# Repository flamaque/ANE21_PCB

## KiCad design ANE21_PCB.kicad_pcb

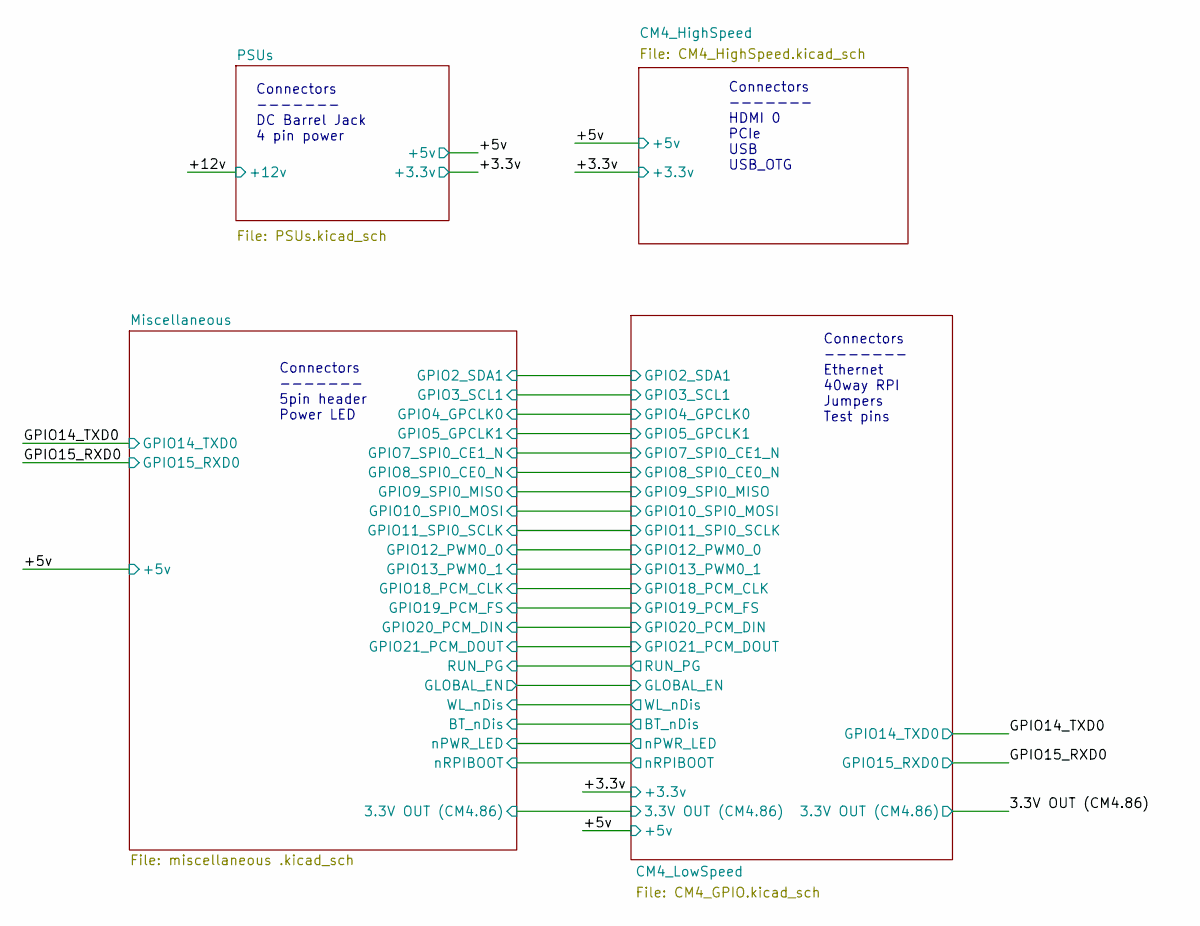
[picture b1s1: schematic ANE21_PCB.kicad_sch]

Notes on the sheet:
Connectors ------- DC Barrel Jack 4 pin power
Connectors ------- Ethernet 40way RPI Jumpers Test pins
Connectors ------- 5pin header Power LED
Connectors ------- HDMI 0 PCIe USB USB_OTG

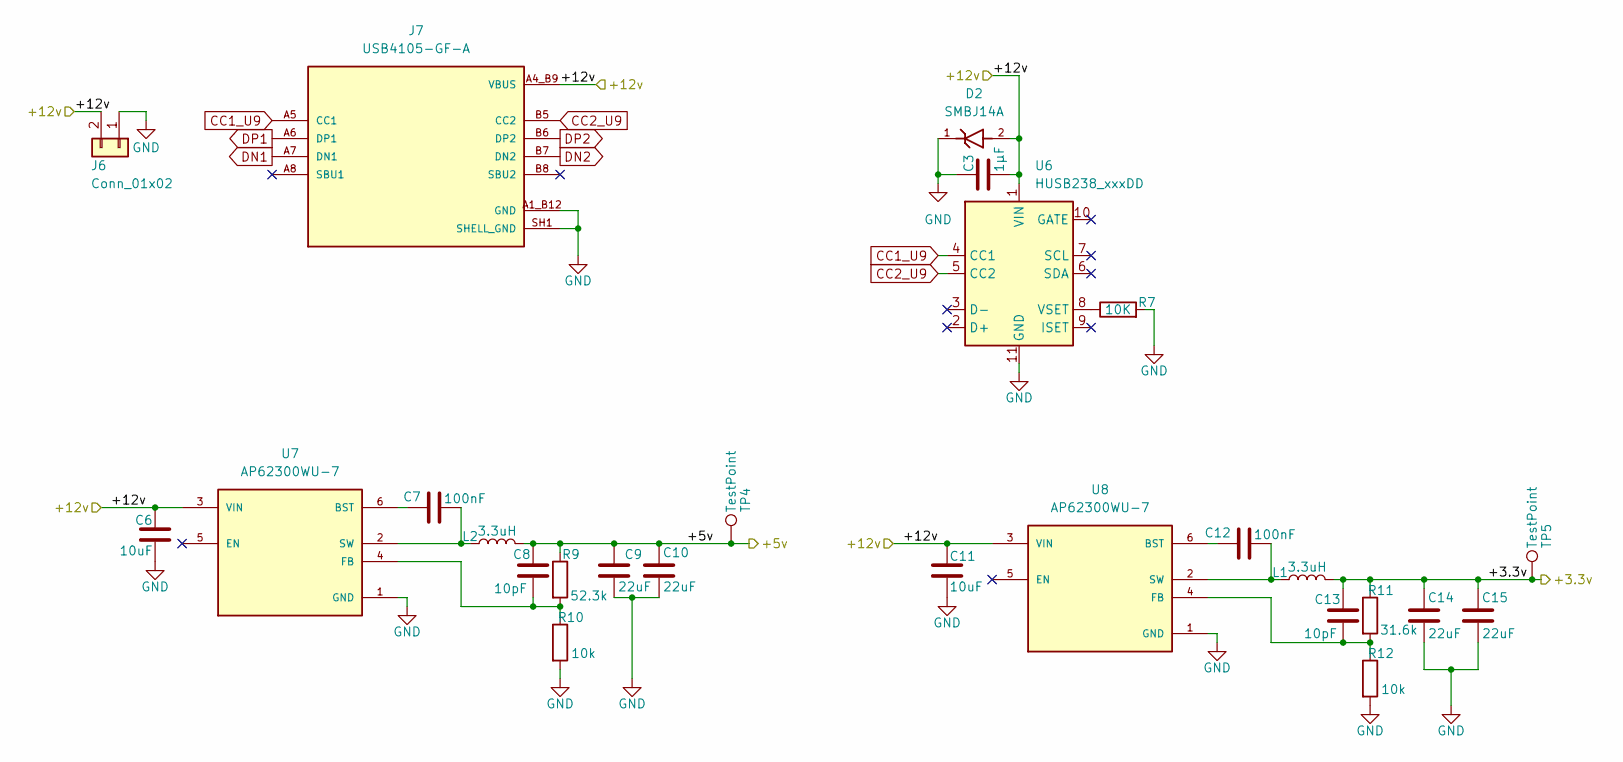
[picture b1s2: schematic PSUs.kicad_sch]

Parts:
C3: 1µF; C_0402_1005Metric_Pad0.74x0.62mm_HandSolder
C6, C11: 10uF; C_0402_1005Metric_Pad0.74x0.62mm_HandSolder
C7, C12: 100nF; C_0402_1005Metric_Pad0.74x0.62mm_HandSolder
C8, C13: 10pF; C_0402_1005Metric_Pad0.74x0.62mm_HandSolder
C9, C10, C14, C15: 22uF; C_0402_1005Metric_Pad0.74x0.62mm_HandSolder
D2: SMBJ14A; DIOM5436X261N; PARTREV JC.07/04/25 v4
J6: Conn_01x02; TerminalBlock_PhoenixTerminalBlock_Phoenix_MKDS-1,5-2-5.08_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
J7: USB4105-GF-A; GCT_USB4105-GF-A; PARTREV B4
L1, L2: 3.3uH; IND_1255AY-3R3N=P3
R7: 10K; R_0402_1005Metric_Pad0.72x0.64mm_HandSolder
R9: 52.3k; R_0402_1005Metric_Pad0.72x0.64mm_HandSolder
R10, R12: 10k; R_0402_1005Metric_Pad0.72x0.64mm_HandSolder
R11: 31.6k; R_0402_1005Metric_Pad0.72x0.64mm_HandSolder
TP4, TP5: TestPoint; TestPoint_Pad_2.0x2.0mm
U6: HUSB238_xxxDD; WDFN-10-1EP_3x3mm_P0.5mm_EP1.8x2.5mm
U7, U8: AP62300WU-7; SOT95P280X100-6N; PARTREV Rev. 3 - 2; DigiKey_Part_Number 31-AP62300WU-7CT-ND

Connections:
/+3.3v: C13.2, C14.2, C15.2, L1.2, R11.1, TP5.1; also elsewhere on the board
CC1_U9: J7.A5 (CC1), U6.4 (CC1); also elsewhere on the board
CC2_U9: J7.B5 (CC2), U6.5 (CC2); also elsewhere on the board
GND: C3.1, C6.2, C9.1, C10.1, C11.2, C14.1, C15.1, D2.1, J6.1, J7.A1_B12 (GND), J7.B1_A12 (GND), J7.SH1 (SHELL_GND), J7.SH2 (SHELL_GND), J7.SH3 (SHELL_GND), J7.SH4 (SHELL_GND), R7.2, R10.2, R12.2, U6.11 (GND), U7.1 (GND), U8.1 (GND); also elsewhere on the board
unnamed: R7.1, U6.8 (VSET)
unnamed: C7.1, U7.6 (BST)
unnamed: C8.1, R9.2, R10.1, U7.4 (FB)
unnamed: C7.2, L2.1, U7.2 (SW)
unnamed: C12.1, U8.6 (BST)
unnamed: C13.1, R11.2, R12.1, U8.4 (FB)
unnamed: C12.2, L1.1, U8.2 (SW)
VBUS: C8.2, C9.2, C10.2, L2.2, R9.1, TP4.1; also elsewhere on the board
VBUS-PD: C3.2, C6.1, C11.1, D2.2, J6.2, J7.A4_B9 (VBUS), J7.B4_A9 (VBUS), U6.1 (VIN), U7.3 (VIN), U8.3 (VIN); also elsewhere on the board

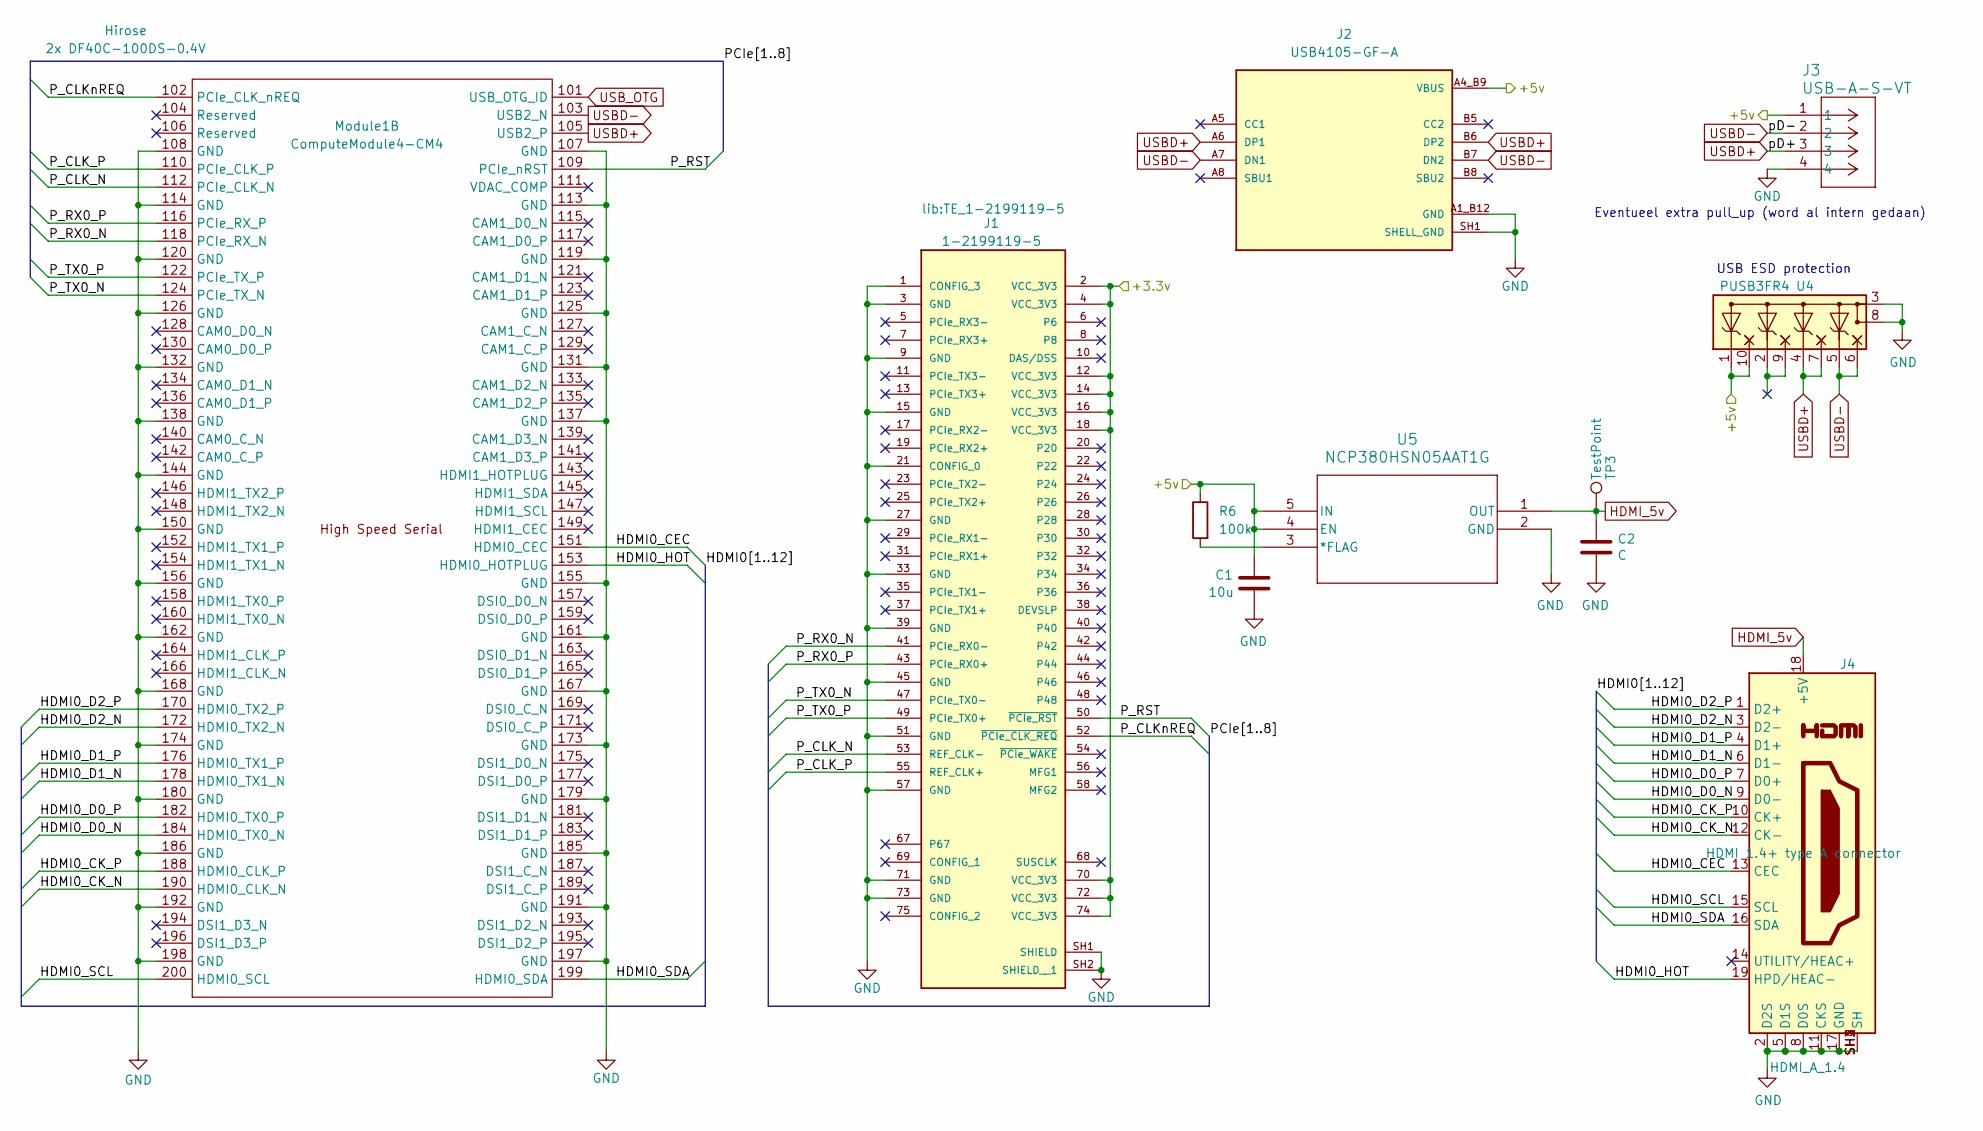
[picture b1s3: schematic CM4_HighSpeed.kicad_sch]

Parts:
C1: 10u; C_0402_1005Metric_Pad0.74x0.62mm_HandSolder; Part Description 0.1uF 10% 16V Ceramic Capacitor X7R 040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
C2: C; C_0402_1005Metric_Pad0.74x0.62mm_HandSolder; Part Description 0.1uF 10% 16V Ceramic Capacitor X7R 040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
J1: 1-2199119-5; TE_1-2199119-5
J2: USB4105-GF-A; GCT_USB4105-GF-A; PARTREV B4
J3: USB-A-S-VT; CONN_USB-A-S-VT_ADM
J4: HDMI_A_1.4; AMPHENOL_10029449-111RLF; Part Description HDMI Connector, Right Angle, 19 Contact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
Module1: ComputeModule4-CM4; Raspberry-Pi-4-Compute-Module
R6: 100k; R_0402_1005Metric_Pad0.72x0.64mm_HandSolder
TP3: TestPoint; TestPoint_Pad_2.0x2.0mm
U4: PUSB3FR4; SOT1176-1
U5: NCP380HSN05AAT1G; TSOP-5_ONS

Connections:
/+3.3v: J1.2 (VCC_3V3), J1.4 (VCC_3V3), J1.12 (VCC_3V3), J1.14 (VCC_3V3), J1.16 (VCC_3V3), J1.18 (VCC_3V3), J1.70 (VCC_3V3), J1.72 (VCC_3V3), J1.74 (VCC_3V3); also elsewhere on the board
/CM4_HighSpeed/HDMI0_CEC: J4.13 (CEC), Module1.151 (HDMI0_CEC)
/CM4_HighSpeed/HDMI0_CK_N: J4.12 (CK-), Module1.190 (HDMI0_CLK_N)
/CM4_HighSpeed/HDMI0_CK_P: J4.10 (CK+), Module1.188 (HDMI0_CLK_P)
/CM4_HighSpeed/HDMI0_D0_N: J4.9 (D0-), Module1.184 (HDMI0_TX0_N)
/CM4_HighSpeed/HDMI0_D0_P: J4.7 (D0+), Module1.182 (HDMI0_TX0_P)
/CM4_HighSpeed/HDMI0_D1_N: J4.6 (D1-), Module1.178 (HDMI0_TX1_N)
/CM4_HighSpeed/HDMI0_D1_P: J4.4 (D1+), Module1.176 (HDMI0_TX1_P)
/CM4_HighSpeed/HDMI0_D2_N: J4.3 (D2-), Module1.172 (HDMI0_TX2_N)
/CM4_HighSpeed/HDMI0_D2_P: J4.1 (D2+), Module1.170 (HDMI0_TX2_P)
/CM4_HighSpeed/HDMI0_HOT: J4.19 (HPD/HEAC-), Module1.153 (HDMI0_HOTPLUG)
/CM4_HighSpeed/HDMI0_SCL: J4.15 (SCL), Module1.200 (HDMI0_SCL)
/CM4_HighSpeed/HDMI0_SDA: J4.16 (SDA), Module1.199 (HDMI0_SDA)
/CM4_HighSpeed/P_CLK_N: J1.53 (REF_CLK-), Module1.112 (PCIe_CLK_N)
/CM4_HighSpeed/P_CLK_P: J1.55 (REF_CLK+), Module1.110 (PCIe_CLK_P)
/CM4_HighSpeed/P_CLKnREQ: J1.52 (~PCIe_CLK_REQ), Module1.102 (PCIe_CLK_nREQ)
/CM4_HighSpeed/P_RST: J1.50 (~PCIe_RST), Module1.109 (PCIe_nRST)
/CM4_HighSpeed/P_RX0_N: J1.41 (PCIe_RX0-), Module1.118 (PCIe_RX_N)
/CM4_HighSpeed/P_RX0_P: J1.43 (PCIe_RX0+), Module1.116 (PCIe_RX_P)
/CM4_HighSpeed/P_TX0_N: J1.47 (PCIe_TX0-), Module1.124 (PCIe_TX_N)
/CM4_HighSpeed/P_TX0_P: J1.49 (PCIe_TX0+), Module1.122 (PCIe_TX_P)
GND: C1.2, C2.2, J1.1 (CONFIG_3), J1.3 (GND), J1.9 (GND), J1.15 (GND), J1.21 (CONFIG_0), J1.27 (GND), J1.33 (GND), J1.39 (GND), J1.45 (GND), J1.51 (GND), J1.57 (GND), J1.71 (GND), J1.73 (GND), J1.SH1 (SHIELD), J1.SH2 (SHIELD__1), J2.A1_B12 (GND), J2.B1_A12 (GND), J2.SH1 (SHELL_GND), J2.SH2 (SHELL_GND), J2.SH3 (SHELL_GND), J2.SH4 (SHELL_GND), J3.4, J4.2 (D2S), J4.5 (D1S), J4.8 (D0S), J4.11 (CKS), J4.17 (GND), J4.SH1 (SH), J4.SH2 (SH), J4.SH3 (SH), J4.SH4 (SH), Module1.107 (GND), Module1.108 (GND), Module1.113 (GND), Module1.114 (GND), Module1.119 (GND), Module1.120 (GND), Module1.125 (GND), Module1.126 (GND), Module1.131 (GND), Module1.132 (GND), Module1.137 (GND), Module1.138 (GND), Module1.144 (GND), Module1.150 (GND), Module1.155 (GND), Module1.156 (GND), Module1.161 (GND), Module1.162 (GND), Module1.167 (GND), Module1.168 (GND), Module1.173 (GND), Module1.174 (GND), Module1.179 (GND), Module1.180 (GND), Module1.185 (GND), Module1.186 (GND), Module1.191 (GND), Module1.192 (GND), Module1.197 (GND), Module1.198 (GND), U4.3 (GND), U4.8 (GND), U5.2 (GND); also elsewhere on the board
HDMI_5v: C2.1, J4.18 (+5V), TP3.1, U5.1 (OUT)
unnamed: R6.2, U5.3 (*FLAG)
USBD+: J2.A6 (DP1), J2.B6 (DP2), J3.3, Module1.105 (USB2_P), U4.4 (In_1+), U4.7 (Out_1+)
USBD-: J2.A7 (DN1), J2.B7 (DN2), J3.2, Module1.103 (USB2_N), U4.5 (In_1-), U4.6 (Out_1+)
USB_OTG: Module1.101 (USB_OTG_ID)
VBUS: C1.1, J2.A4_B9 (VBUS), J2.B4_A9 (VBUS), J3.1, R6.1, U4.1 (In_1+), U4.10 (Out_1+), U5.4 (EN), U5.5 (IN); also elsewhere on the board

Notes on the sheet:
USB ESD protection
Eventueel extra pull_up (word al intern gedaan)

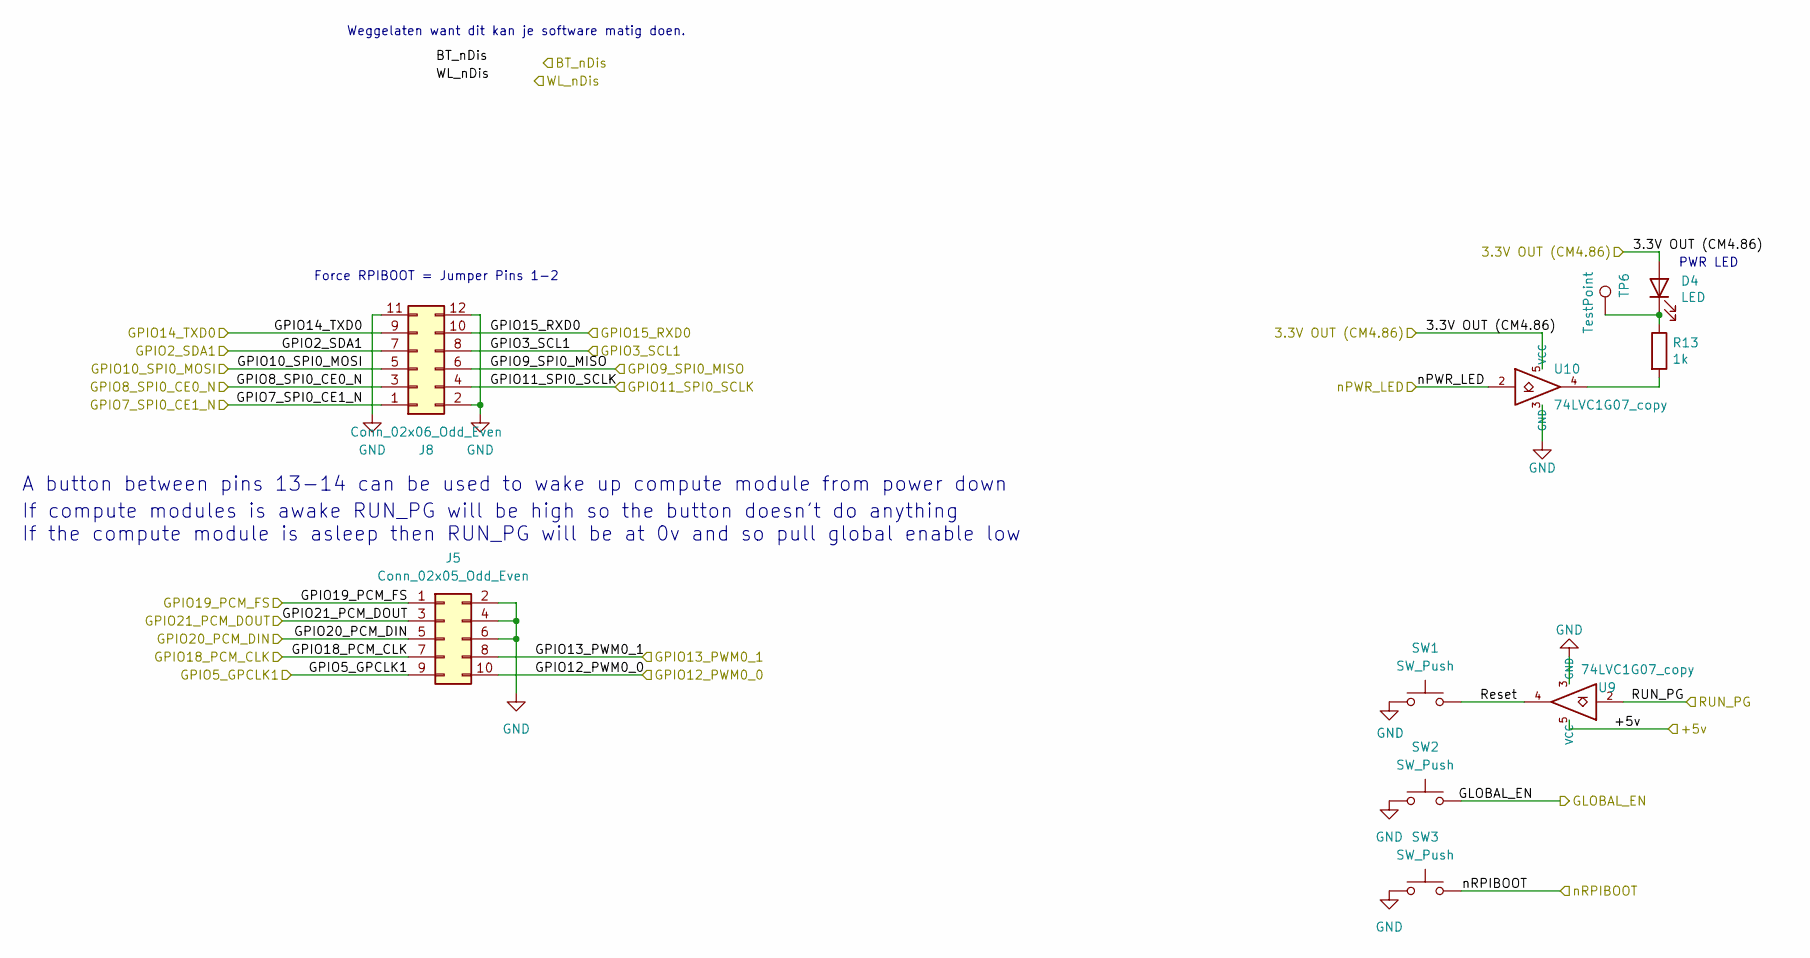
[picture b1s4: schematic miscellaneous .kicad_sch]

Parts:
D4: LED; LED_0603_1608Metric; Part Description Red 620nm LED Indication - Discrete 2.2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
J5: Conn_02x05_Odd_Even; PinHeader_2x05_P2.54mm_Vertical
J8: Conn_02x06_Odd_Even; PinHeader_2x06_P2.54mm_Vertical
R13: 1k; R_0402_1005Metric_Pad0.72x0.64mm_HandSolder; Part Description Resistor 1K M1005 1% 63mW
SW1, SW2, SW3: SW_Push; SW_SPST_TS-1088-xR020
TP6: TestPoint; TestPoint_Pad_2.0x2.0mm
U9, U10: 74LVC1G07_copy; SOT-353_SC-70-5; Part Description Buffer, Non-Inverting 1 Element 1 Bit p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

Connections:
/3.3V OUT (CM4.86): D4.2 (A), U10.5 (VCC); also elsewhere on the board
/CM4_LowSpeed/GLOBAL_EN: SW2.2; also elsewhere on the board
/CM4_LowSpeed/GPIO2_SDA1: J8.7; also elsewhere on the board
/CM4_LowSpeed/GPIO3_SCL1: J8.8; also elsewhere on the board
/CM4_LowSpeed/GPIO5_GPCLK1: J5.9; also elsewhere on the board
/CM4_LowSpeed/GPIO7_SPI0_CE1_N: J8.1; also elsewhere on the board
/CM4_LowSpeed/GPIO8_SPI0_CE0_N: J8.3; also elsewhere on the board
/CM4_LowSpeed/GPIO9_SPI0_MISO: J8.6; also elsewhere on the board
/CM4_LowSpeed/GPIO10_SPI0_MOSI: J8.5; also elsewhere on the board
/CM4_LowSpeed/GPIO11_SPI0_SCLK: J8.4; also elsewhere on the board
/CM4_LowSpeed/GPIO12_PWM0_0: J5.10; also elsewhere on the board
/CM4_LowSpeed/GPIO13_PWM0_1: J5.8; also elsewhere on the board
/CM4_LowSpeed/GPIO18_PCM_CLK: J5.7; also elsewhere on the board
/CM4_LowSpeed/GPIO19_PCM_FS: J5.1; also elsewhere on the board
/CM4_LowSpeed/GPIO20_PCM_DIN: J5.5; also elsewhere on the board
/CM4_LowSpeed/GPIO21_PCM_DOUT: J5.3; also elsewhere on the board
/CM4_LowSpeed/RUN_PG: U9.2; also elsewhere on the board
/CM4_LowSpeed/nPWR_LED: U10.2; also elsewhere on the board
/CM4_LowSpeed/nRPIBOOT: SW3.2; also elsewhere on the board
/GPIO14_TXD0: J8.9; also elsewhere on the board
/GPIO15_RXD0: J8.10; also elsewhere on the board
/Miscellaneous/Reset: SW1.2, U9.4
GND: J5.2, J5.4, J5.6, J8.2, J8.11, J8.12, SW1.1, SW2.1, SW3.1, U9.3 (GND), U10.3 (GND); also elsewhere on the board
unnamed: D4.1 (K), R13.1, TP6.1
unnamed: R13.2, U10.4
VBUS: U9.5 (VCC); also elsewhere on the board

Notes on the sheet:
A button between pins 13-14 can be used to wake up compute module from power down
If compute modules is awake RUN_PG will be high so the button doesn't do anything If the compute module is asleep then RUN_PG will be at 0v and so pull global enable low
Weggelaten want dit kan je software matig doen.
Force RPIBOOT = Jumper Pins 1-2
PWR LED

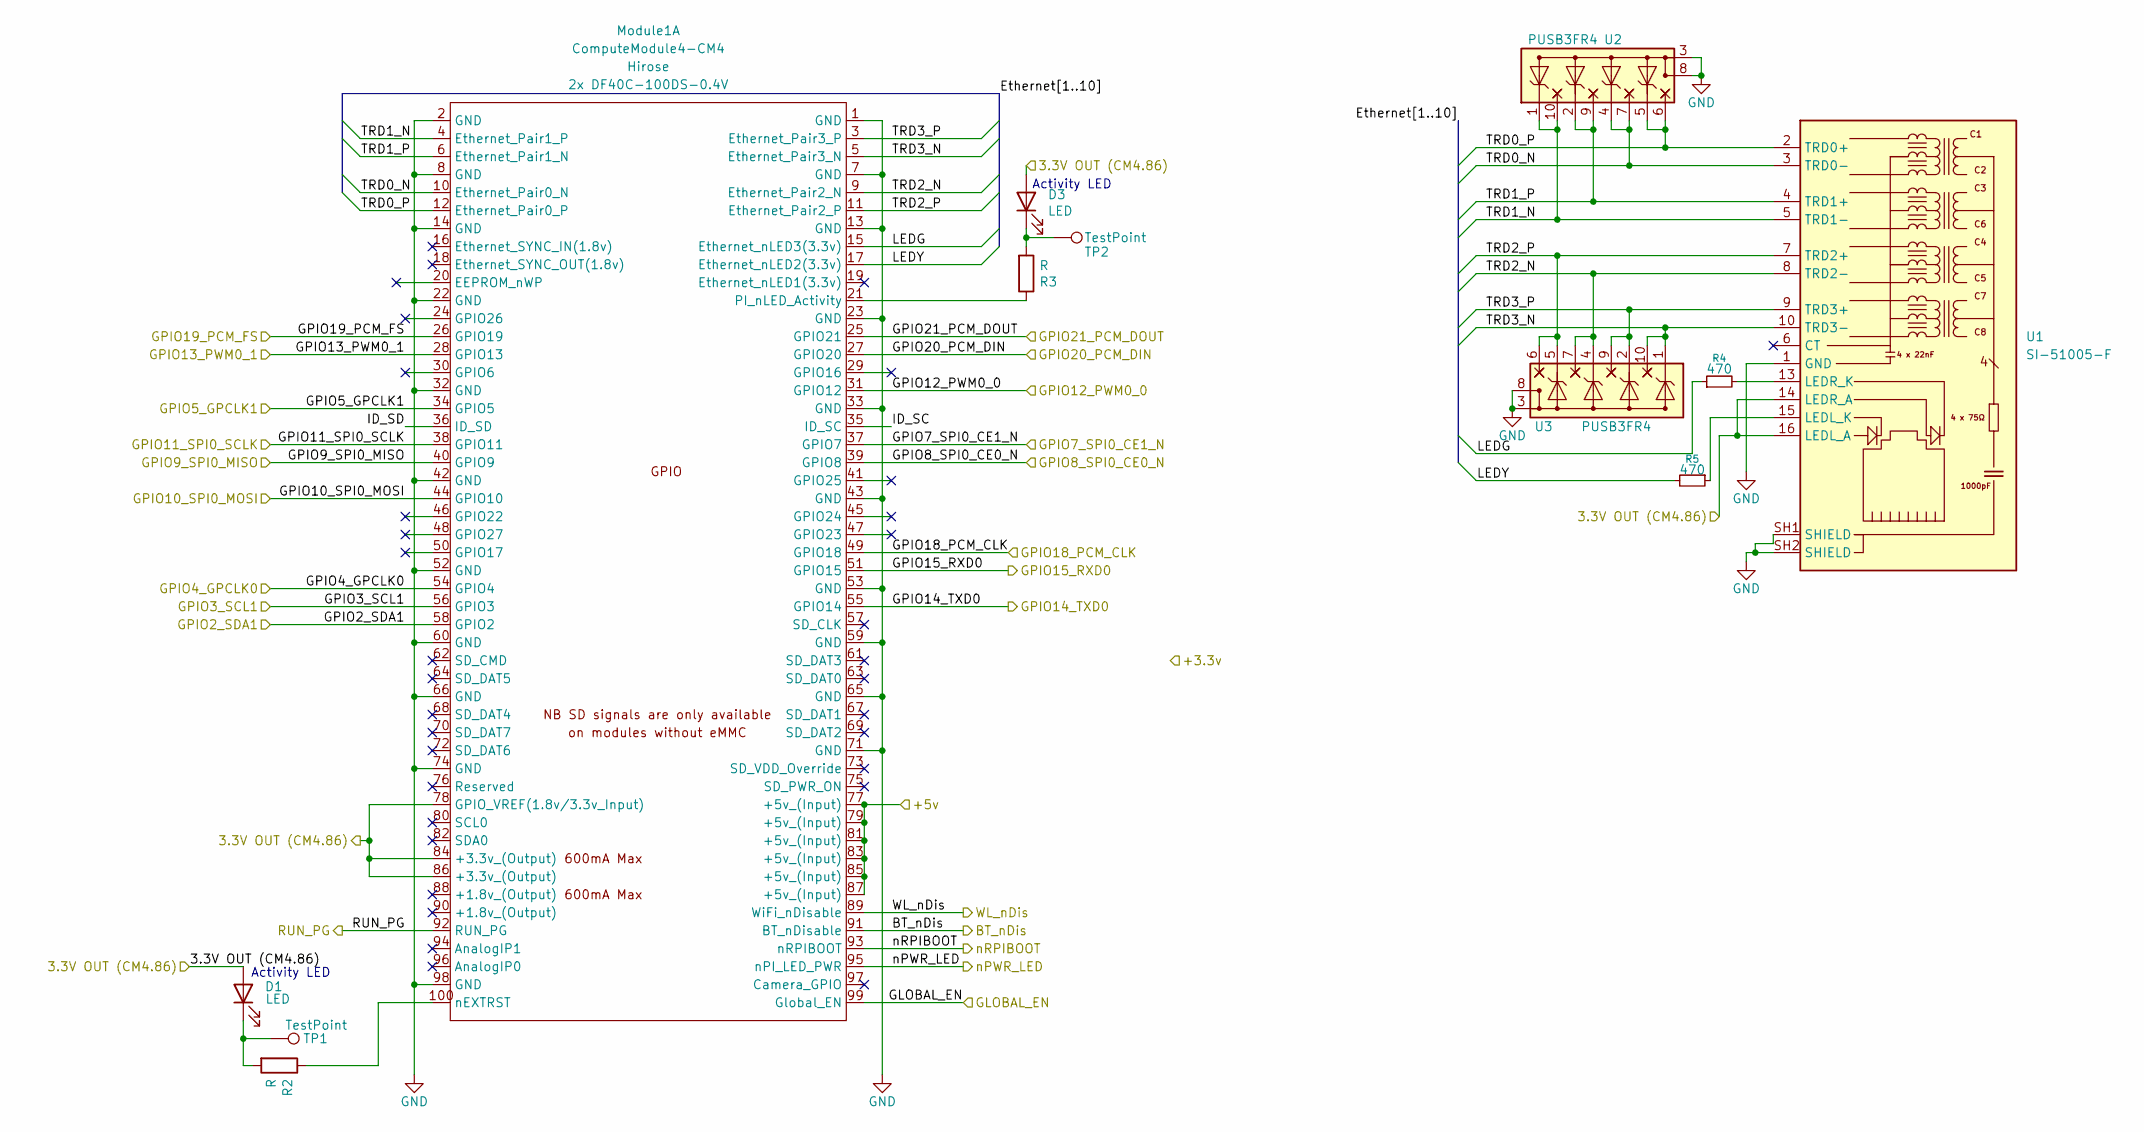
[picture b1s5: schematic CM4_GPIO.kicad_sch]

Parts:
D1, D3: LED; LED_0603_1608Metric; Part Description Green 572nm LED Indication - Discrete 2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
Module1: ComputeModule4-CM4; Raspberry-Pi-4-Compute-Module
R2, R3: R; R_0402_1005Metric_Pad0.72x0.64mm_HandSolder; Part Description Resistor 1K M1005 1% 63mW
R4, R5: 470; R_0402_1005Metric_Pad0.72x0.64mm_HandSolder
TP1, TP2: TestPoint; TestPoint_Pad_2.0x2.0mm
U1: SI-51005-F; BEL_SI-51005-F
U2, U3: PUSB3FR4; SOT1176-1

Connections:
/3.3V OUT (CM4.86): D1.2 (A), D3.2 (A), Module1.78 (GPIO_VREF(1.8v/3.3v_Input)), Module1.84 (+3.3v_(Output)), Module1.86 (+3.3v_(Output)), U1.14 (LEDR_A), U1.16 (LEDL_A); also elsewhere on the board
/CM4_LowSpeed/BT_nDis: Module1.91 (BT_nDisable)
/CM4_LowSpeed/GLOBAL_EN: Module1.99 (Global_EN); also elsewhere on the board
/CM4_LowSpeed/GPIO2_SDA1: Module1.58 (GPIO2); also elsewhere on the board
/CM4_LowSpeed/GPIO3_SCL1: Module1.56 (GPIO3); also elsewhere on the board
/CM4_LowSpeed/GPIO4_GPCLK0: Module1.54 (GPIO4)
/CM4_LowSpeed/GPIO5_GPCLK1: Module1.34 (GPIO5); also elsewhere on the board
/CM4_LowSpeed/GPIO7_SPI0_CE1_N: Module1.37 (GPIO7); also elsewhere on the board
/CM4_LowSpeed/GPIO8_SPI0_CE0_N: Module1.39 (GPIO8); also elsewhere on the board
/CM4_LowSpeed/GPIO9_SPI0_MISO: Module1.40 (GPIO9); also elsewhere on the board
/CM4_LowSpeed/GPIO10_SPI0_MOSI: Module1.44 (GPIO10); also elsewhere on the board
/CM4_LowSpeed/GPIO11_SPI0_SCLK: Module1.38 (GPIO11); also elsewhere on the board
/CM4_LowSpeed/GPIO12_PWM0_0: Module1.31 (GPIO12); also elsewhere on the board
/CM4_LowSpeed/GPIO13_PWM0_1: Module1.28 (GPIO13); also elsewhere on the board
/CM4_LowSpeed/GPIO18_PCM_CLK: Module1.49 (GPIO18); also elsewhere on the board
/CM4_LowSpeed/GPIO19_PCM_FS: Module1.26 (GPIO19); also elsewhere on the board
/CM4_LowSpeed/GPIO20_PCM_DIN: Module1.27 (GPIO20); also elsewhere on the board
/CM4_LowSpeed/GPIO21_PCM_DOUT: Module1.25 (GPIO21); also elsewhere on the board
/CM4_LowSpeed/ID_SC: Module1.35 (ID_SC)
/CM4_LowSpeed/ID_SD: Module1.36 (ID_SD)
/CM4_LowSpeed/LEDG: Module1.15 (Ethernet_nLED3(3.3v)), R4.1
/CM4_LowSpeed/LEDY: Module1.17 (Ethernet_nLED2(3.3v)), R5.2
/CM4_LowSpeed/RUN_PG: Module1.92 (RUN_PG); also elsewhere on the board
/CM4_LowSpeed/TRD0_N: Module1.10 (Ethernet_Pair0_N), U1.3 (TRD0-), U2.4 (In_1+), U2.7 (Out_1+)
/CM4_LowSpeed/TRD0_P: Module1.12 (Ethernet_Pair0_P), U1.2 (TRD0+), U2.5 (In_1-), U2.6 (Out_1+)
/CM4_LowSpeed/TRD1_N: Module1.4 (Ethernet_Pair1_P), U1.5 (TRD1-), U2.1 (In_1+), U2.10 (Out_1+)
/CM4_LowSpeed/TRD1_P: Module1.6 (Ethernet_Pair1_N), U1.4 (TRD1+), U2.2 (In_1-), U2.9 (Out_1+)
/CM4_LowSpeed/TRD2_N: Module1.9 (Ethernet_Pair2_N), U1.8 (TRD2-), U3.4 (In_1+), U3.7 (Out_1+)
/CM4_LowSpeed/TRD2_P: Module1.11 (Ethernet_Pair2_P), U1.7 (TRD2+), U3.5 (In_1-), U3.6 (Out_1+)
/CM4_LowSpeed/TRD3_N: Module1.5 (Ethernet_Pair3_N), U1.10 (TRD3-), U3.1 (In_1+), U3.10 (Out_1+)
/CM4_LowSpeed/TRD3_P: Module1.3 (Ethernet_Pair3_P), U1.9 (TRD3+), U3.2 (In_1-), U3.9 (Out_1+)
/CM4_LowSpeed/WL_nDis: Module1.89 (WiFi_nDisable)
/CM4_LowSpeed/nPWR_LED: Module1.95 (nPI_LED_PWR); also elsewhere on the board
/CM4_LowSpeed/nRPIBOOT: Module1.93 (nRPIBOOT); also elsewhere on the board
/GPIO14_TXD0: Module1.55 (GPIO14); also elsewhere on the board
/GPIO15_RXD0: Module1.51 (GPIO15); also elsewhere on the board
GND: Module1.1 (GND), Module1.2 (GND), Module1.7 (GND), Module1.8 (GND), Module1.13 (GND), Module1.14 (GND), Module1.22 (GND), Module1.23 (GND), Module1.32 (GND), Module1.33 (GND), Module1.42 (GND), Module1.43 (GND), Module1.52 (GND), Module1.53 (GND), Module1.59 (GND), Module1.60 (GND), Module1.65 (GND), Module1.66 (GND), Module1.71 (GND), Module1.74 (GND), Module1.98 (GND), U1.1 (GND), U1.SH1 (SHIELD), U1.SH2 (SHIELD), U2.3 (GND), U2.8 (GND), U3.3 (GND), U3.8 (GND); also elsewhere on the board
unnamed: D1.1 (K), R2.2, TP1.1
unnamed: D3.1 (K), R3.2, TP2.1
unnamed: Module1.21 (PI_nLED_Activity), R3.1
unnamed: Module1.100 (nEXTRST), R2.1
unnamed: R5.1, U1.15 (LEDL_K)
unnamed: R4.2, U1.13 (LEDR_K)
VBUS: Module1.77 (+5v_(Input)), Module1.79 (+5v_(Input)), Module1.81 (+5v_(Input)), Module1.83 (+5v_(Input)), Module1.85 (+5v_(Input)), Module1.87 (+5v_(Input)); also elsewhere on the board

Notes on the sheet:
Activity LED

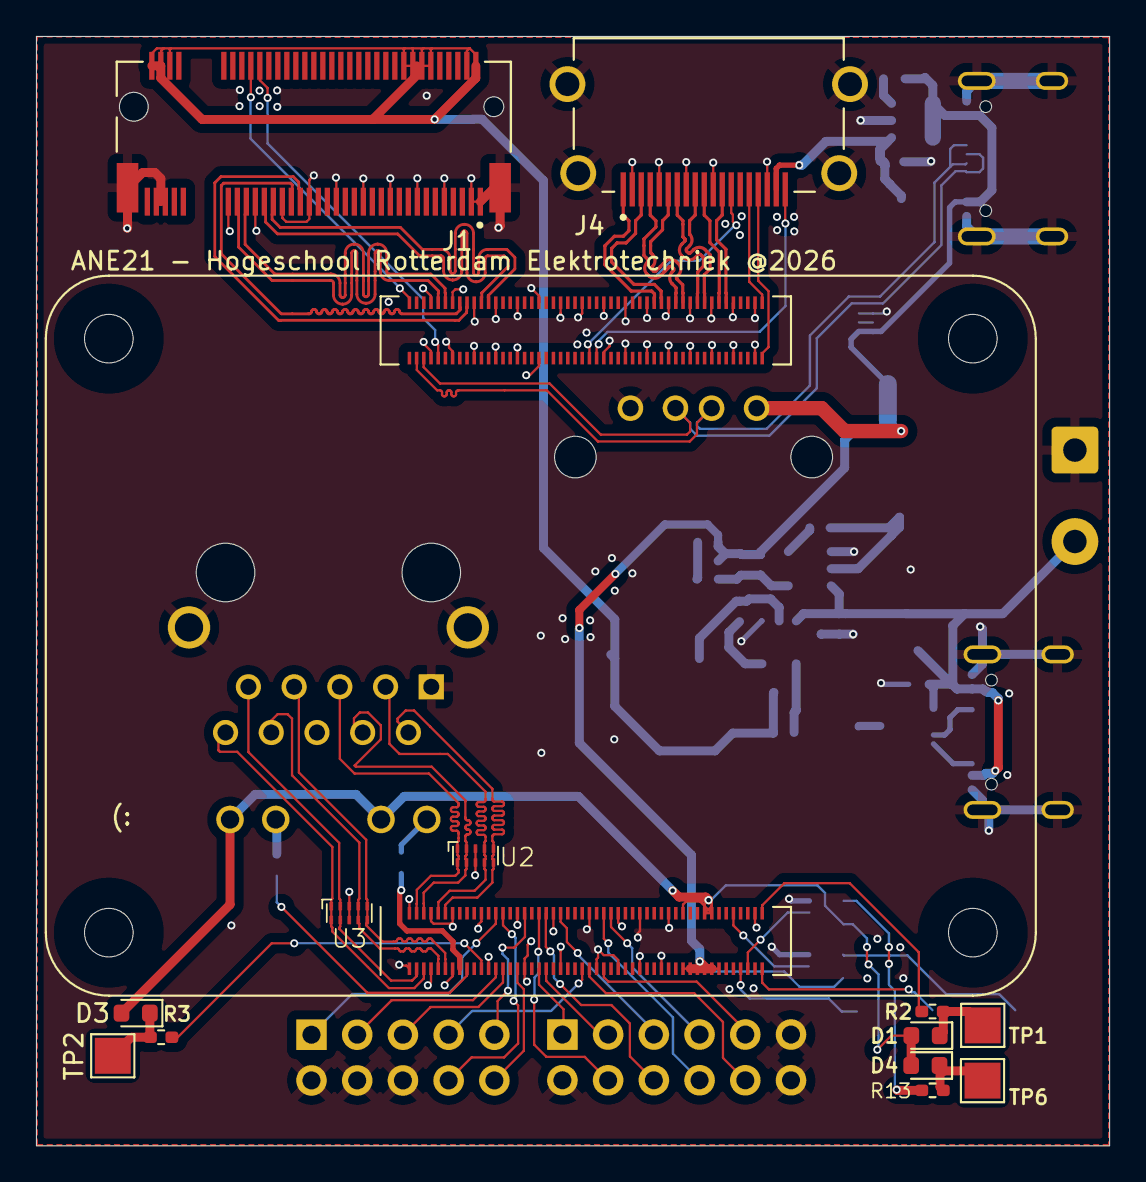
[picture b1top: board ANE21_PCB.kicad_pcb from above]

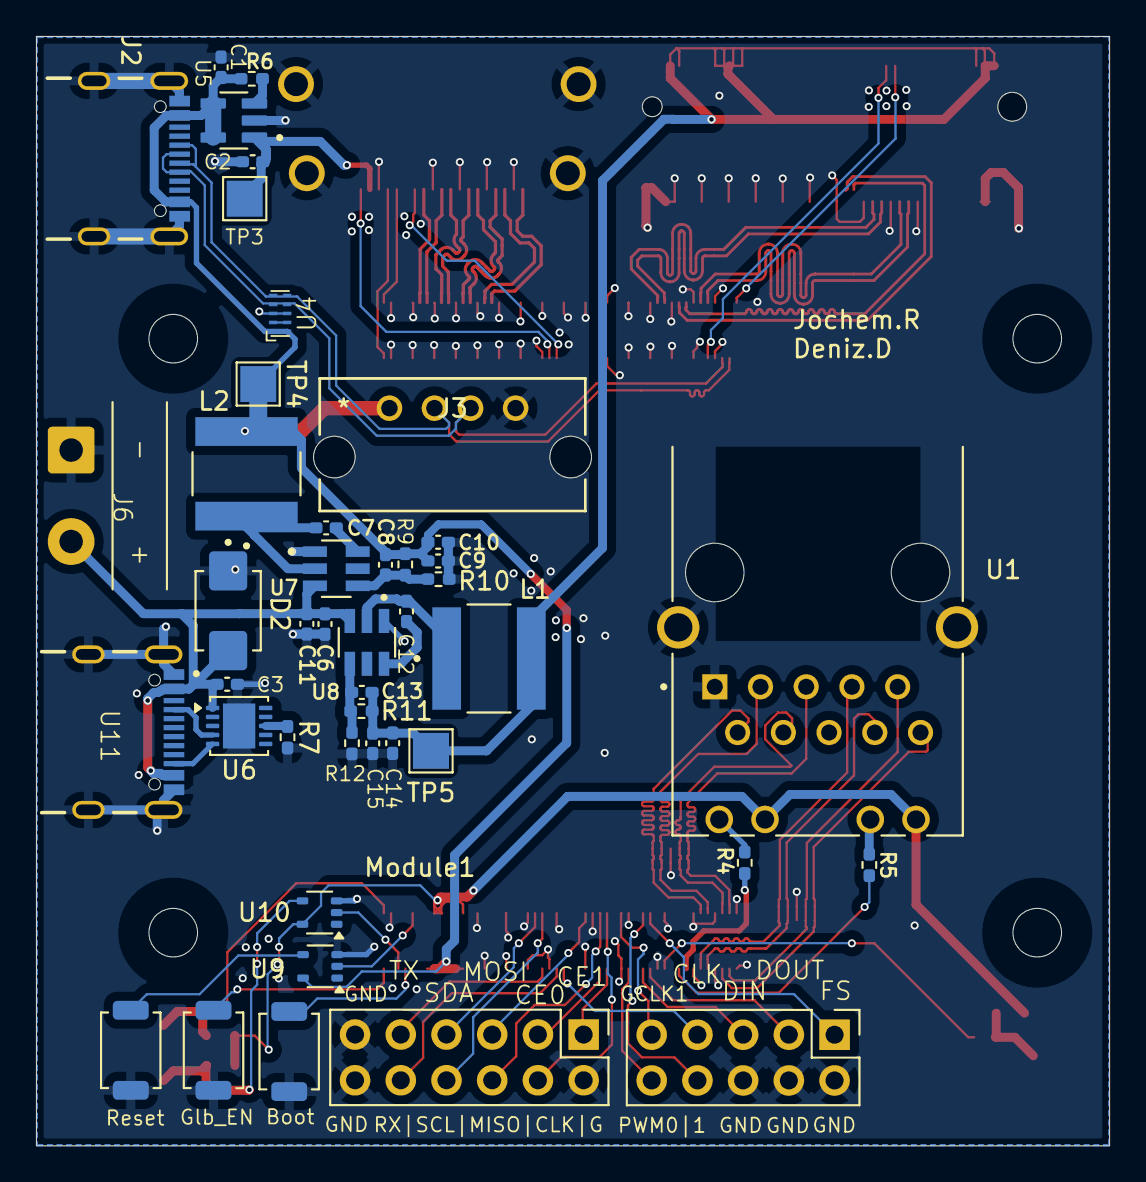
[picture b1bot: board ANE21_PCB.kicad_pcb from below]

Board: 4 copper layers, 59.6 x 61.6 mm, 58 parts (44 on the bottom side), 77 nets.

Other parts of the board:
U11: USB4105-GF-A-PD

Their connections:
CC1_U9: U11.A5 (CC1); also elsewhere on the board
CC2_U9: U11.B5 (CC2); also elsewhere on the board
GND: U11.A1_B12 (GND), U11.B1_A12 (GND), U11.SH1 (SHELL_GND), U11.SH2 (SHELL_GND), U11.SH3 (SHELL_GND), U11.SH4 (SHELL_GND); also elsewhere on the board
VBUS-PD: U11.A4_B9 (VBUS-PD), U11.B4_A9 (VBUS-PD); also elsewhere on the board

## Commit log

2026-02-13 Added footprints and symbols
    Could not find -on SnapEDA- MCWR06X3322FTL, MCMR06X3162FTL and USB-A-S-VT.
    Power load switch NCP380HSN05AAT1G only had footprint on SnapEDA, no symbol.
    Need to update HMDI footprint and symbol to correct one.
2026-02-23 Added symbol for Power switch and Word document replacing google docs
2026-03-02 Added formulas and table with pinout of CM4
2026-03-03 Updated word document
2026-03-03 Added footprints for PCIe and added busses for PCIe and Ethernet
2026-03-03 Woops, forgot the document
2026-03-04 Moved PCIe psu to global psu schematic
2026-03-05 Cleaned up schematics and added gnds and no-connects
2026-03-05 Added USB-C footprint
2026-03-05 USB-c toegeveogd moet alleen nog omvormen
2026-03-05 USB-C afgemaakt
    Ik heb hem apart gepusht. ik ga nu bezig zijn met de HDMI
2026-03-05 Heb mijn documentatie geleverd voor de USB-c en heb een BOM toegevoegd
2026-03-06 Added 3d-models, esd protection, cleaned up and made small start with pcb
2026-03-06 Adjusted the PCB design, changed footprints to 0402 (temp)
2026-03-07 Adjusted netclasses to route differential pairs for PCIe and HDMI. And used JLCPCB to adjust trace width for those
2026-03-07 heb de GPIO aangepast.
    Laten we morgen de stand van zaken bespreken. En overleggen wat we kunnen doen
2026-03-08 Added HDMI traces but have not checked them
2026-03-08 Added lots and lots of traces in PCB design.
2026-03-08 PCB is af. kan je het nog checken?
2026-03-08 Redid the routing and fixed ERC warnings
2026-03-08 Small changes to routes
2026-03-08 definitief ingelverd
2026-03-10 Redid traces with correct requirements, needs double checking.
2026-03-12 Very small changes made, dunno what
2026-03-12 Adjusted 3.3v for CM4 3.3v output, PCIe stayed the same.
2026-03-13 Hehe, smol board now
2026-03-20 heb een kleine tabel gemaakt met de pins
2026-03-25 Changed quite a bit, PCB smoll now
    Redid all traces, replaced HUSB238 with ch224k, made PCB even smaller.
2026-03-26 Changed PD back to HUSB238
2026-03-28 Adjusted footprint Phoenix connector and added some text.
2026-03-30 gerber files gemaakt
2026-04-02 Added datasheets for to-be-ordered components, double checked BOM
2026-04-20 Can't remember
